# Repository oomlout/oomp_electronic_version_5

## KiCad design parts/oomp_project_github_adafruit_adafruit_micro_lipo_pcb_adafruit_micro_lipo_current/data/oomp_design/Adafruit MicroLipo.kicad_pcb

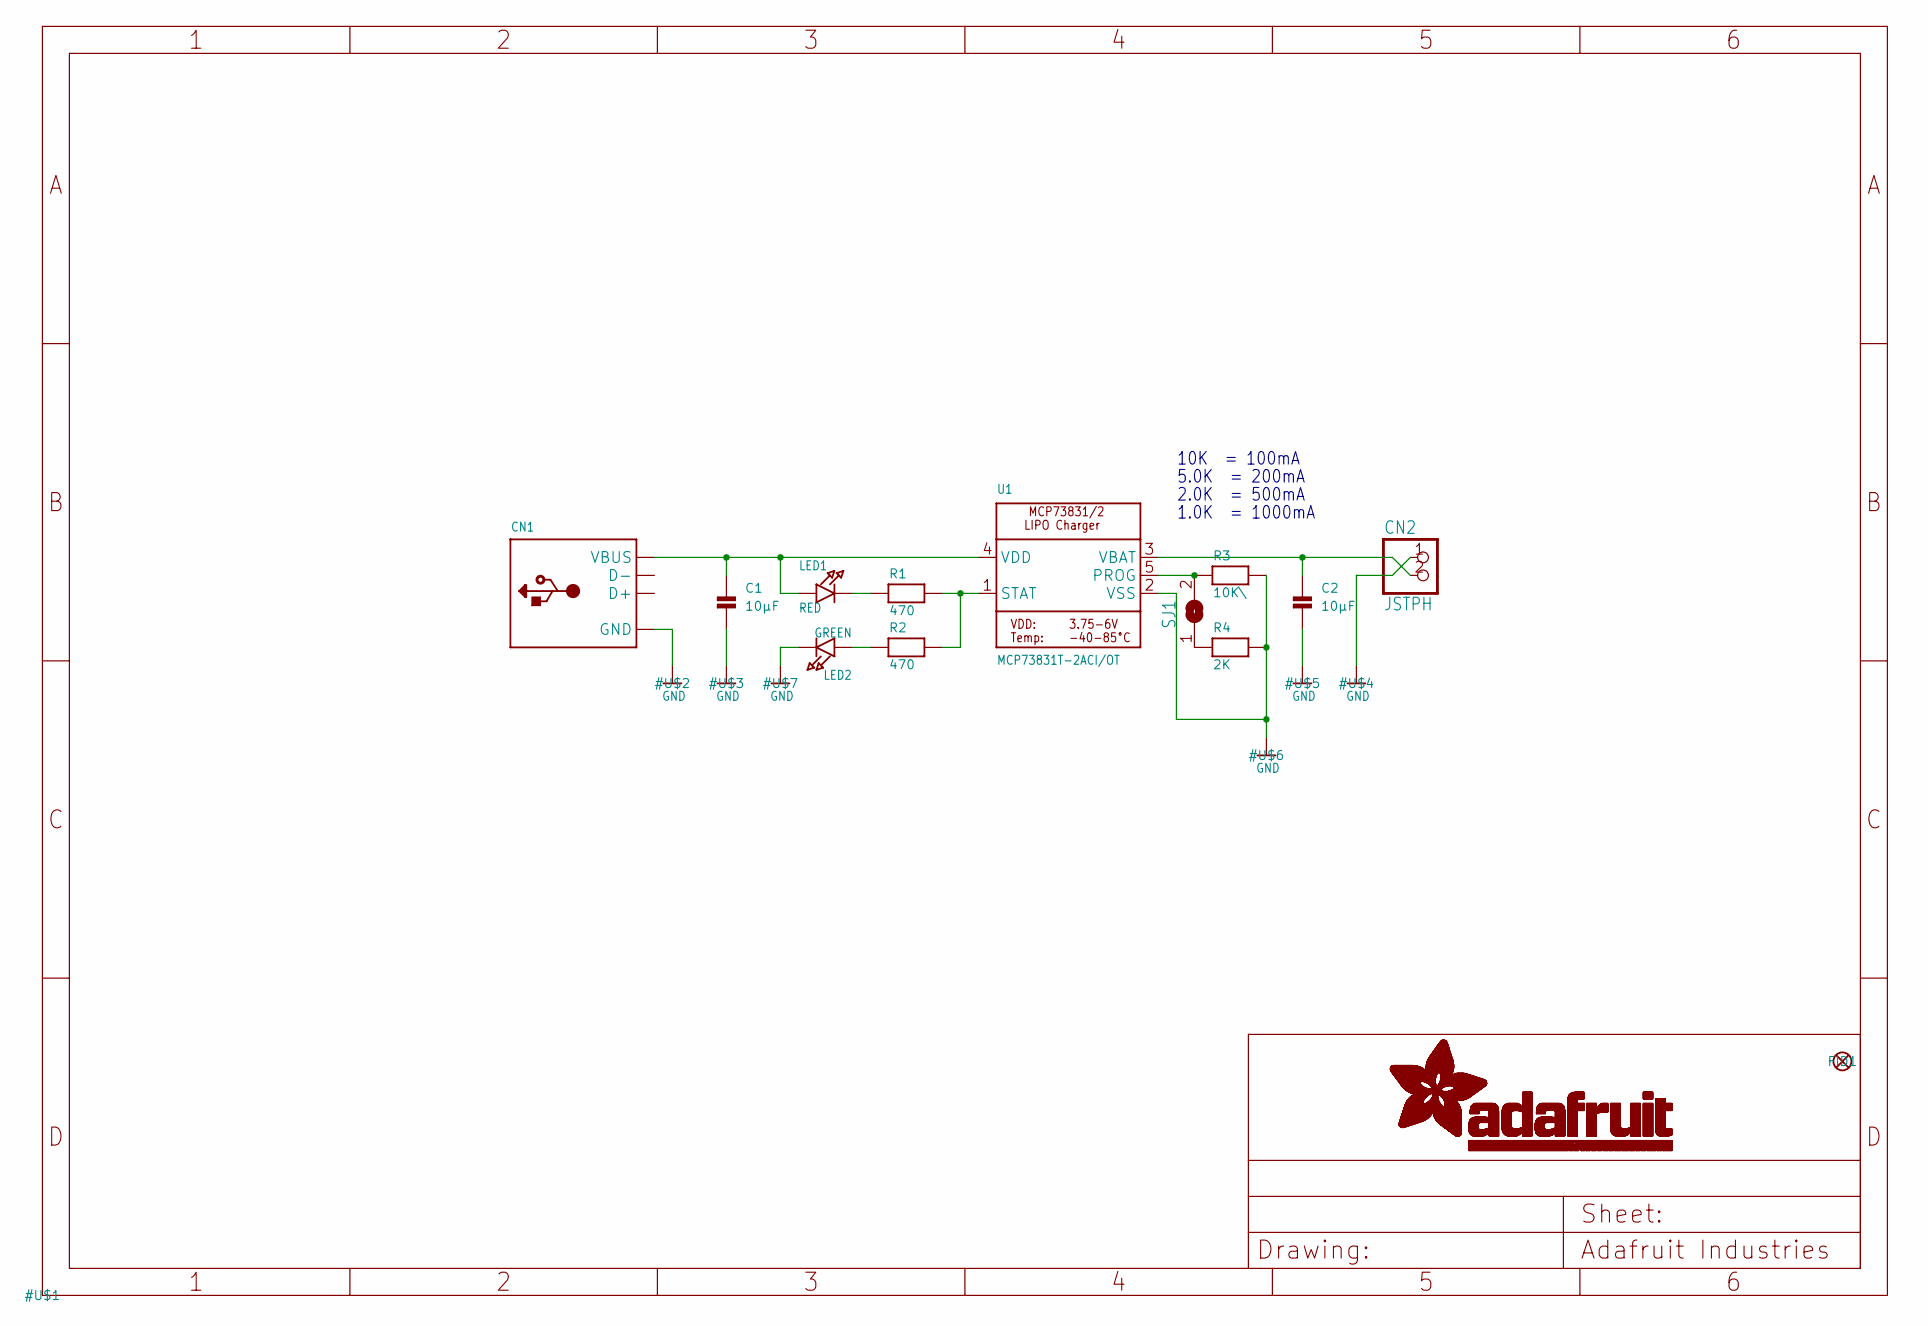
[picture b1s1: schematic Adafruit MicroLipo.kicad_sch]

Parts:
C1, C2: 10µF; 0805
CN1: USB_TYPEAPCB; USBA_PCB
CN2: JSTPH; JSTPH2
FID1: FIDUCIAL""; FIDUCIAL_1MM
LED1: RED; CHIPLED_0805
LED2: GREEN; CHIPLED_0805
R1, R2: 470; 0805
R3: 10K\; 0805
R4: 2K; 0805
SJ1: SOLDERJUMPER; SOLDERJUMPER_ARROW_NOPASTE
U1: MCP73831T-2ACI/OT; SOT23-5

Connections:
GND: C1.2, C2.2, CN1.GND, CN2.1, LED2.C, R3.2, R4.2, U1.2 (VSS)
unnamed: LED1.C, R1.1
unnamed: R1.2, R2.2, U1.1 (STAT)
unnamed: R4.1, SJ1.1
unnamed: R3.1, SJ1.2, U1.5 (PROG)
unnamed: LED2.A, R2.1
VBAT: C2.1, CN2.2, U1.3 (VBAT)
VDD: C1.1, CN1.VCC (VBUS), LED1.A, U1.4 (VDD)

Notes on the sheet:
5.0K = 200mA
10K = 100mA
1.0K = 1000mA
2.0K = 500mA

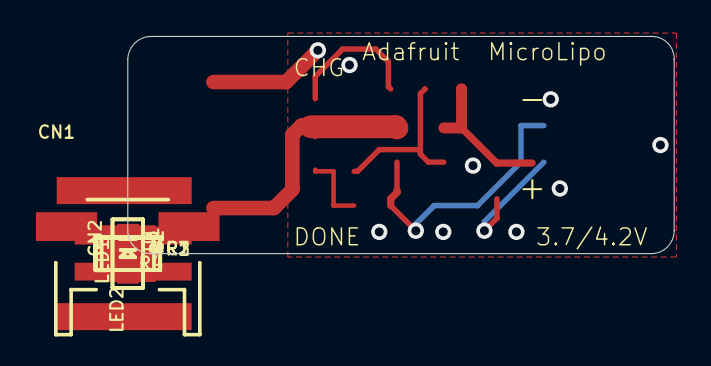
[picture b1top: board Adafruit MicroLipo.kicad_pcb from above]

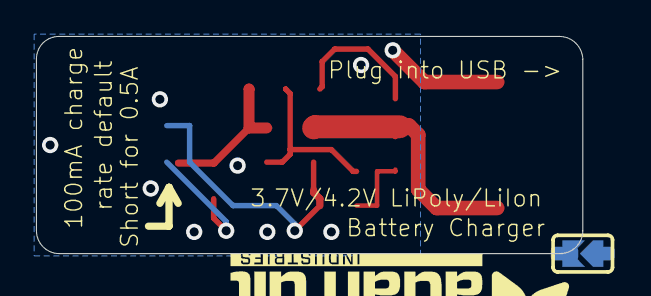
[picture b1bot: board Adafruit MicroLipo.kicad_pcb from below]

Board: 2 copper layers, 30.4 x 12.1 mm, 14 parts (2 on the bottom side), 8 nets.

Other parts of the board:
U$8: ADAFRUIT_TEXT_20MM

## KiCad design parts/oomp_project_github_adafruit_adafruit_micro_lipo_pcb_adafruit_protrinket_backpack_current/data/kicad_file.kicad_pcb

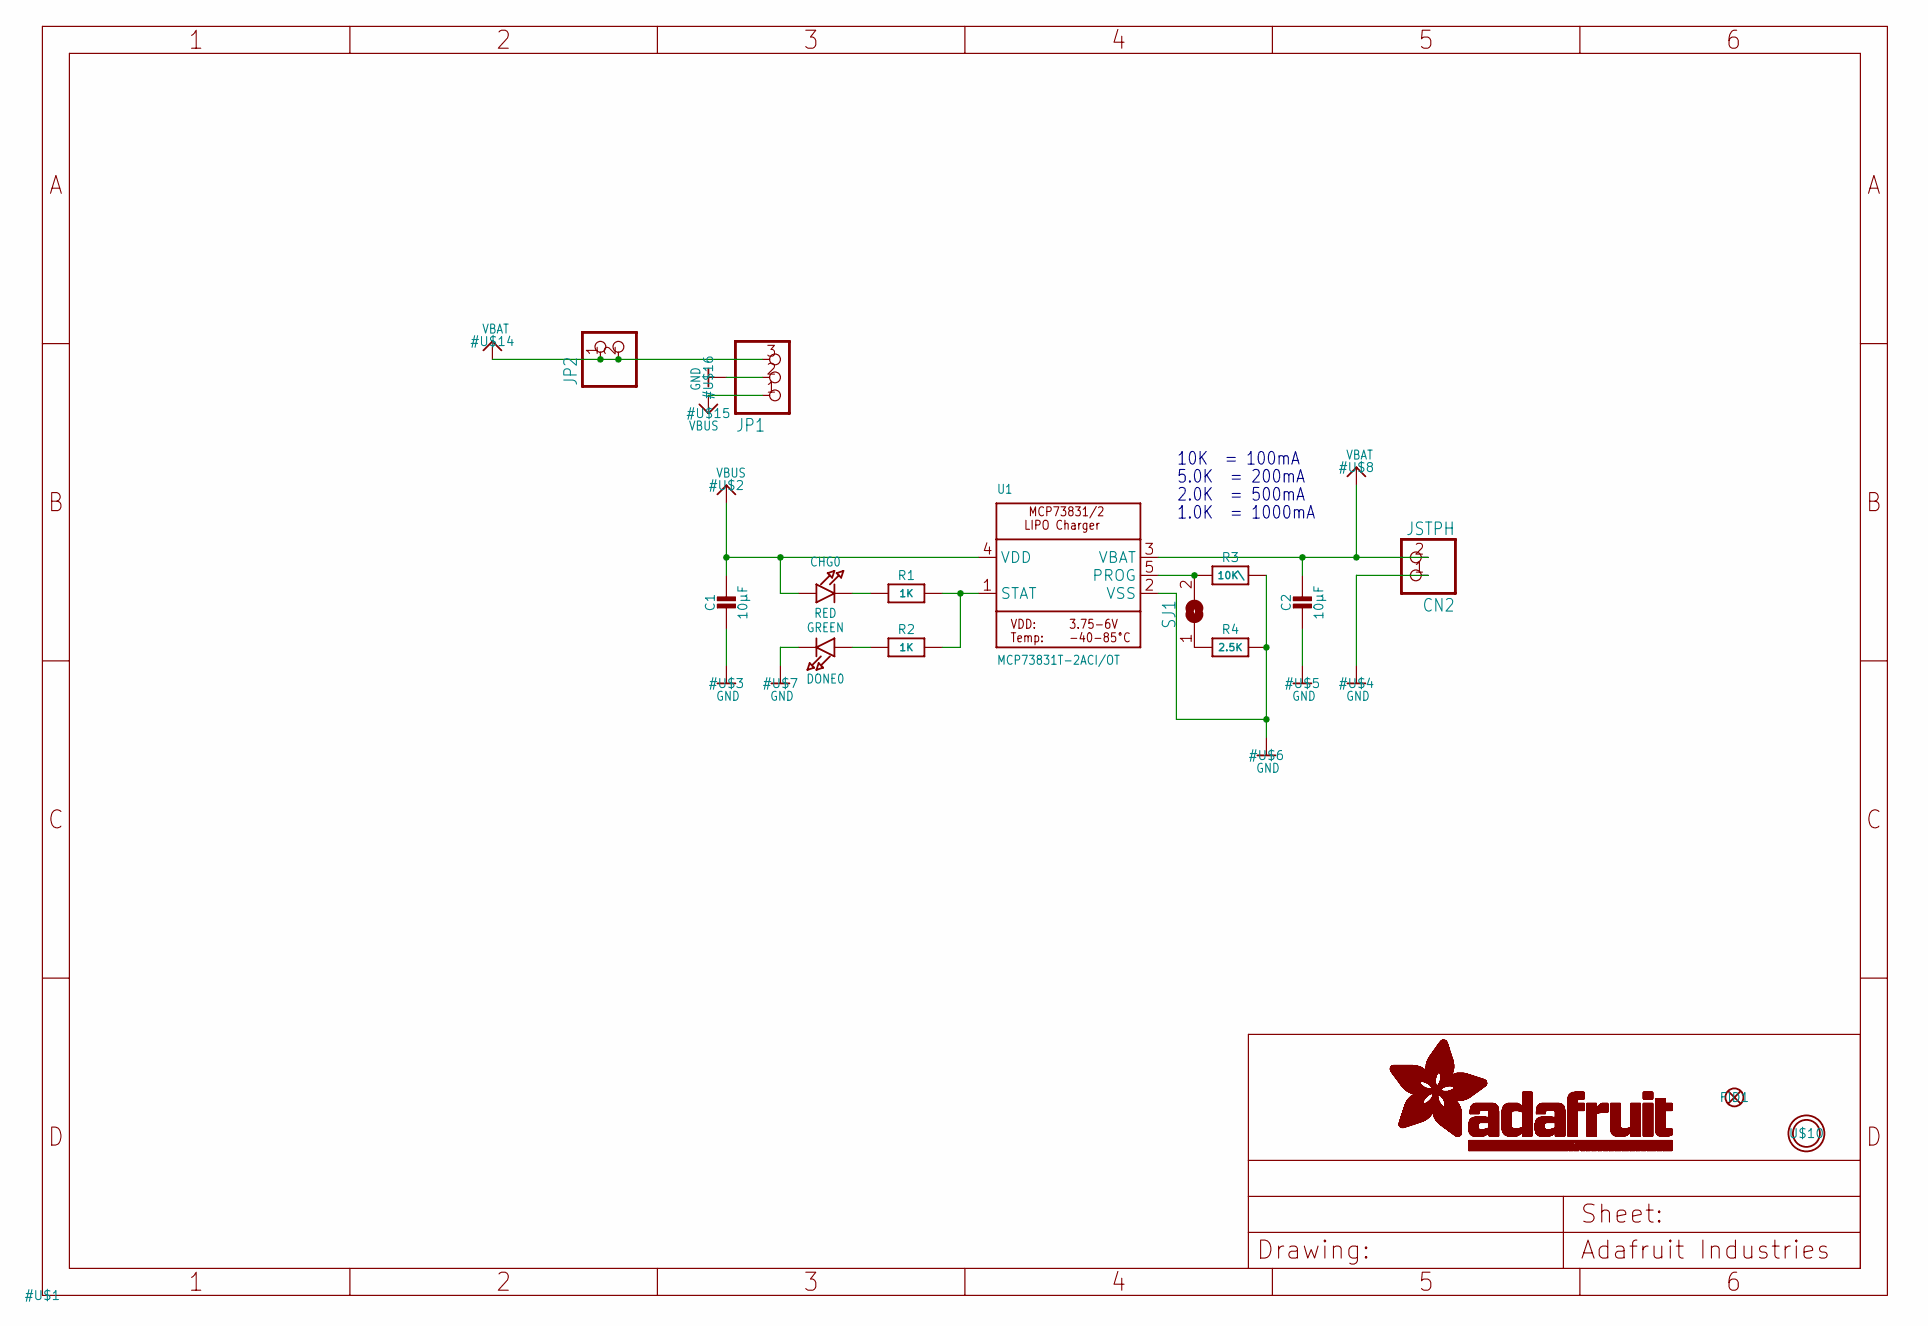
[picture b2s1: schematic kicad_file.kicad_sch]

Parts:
C1, C2: 10µF; 0805-NO
CHG0: RED; CHIPLED_0805_NOOUTLINE
CN2: JSTPH; JSTPH2
DONE0: GREEN; CHIPLED_0805_NOOUTLINE
FID1: FIDUCIAL""; FIDUCIAL_1MM
JP1: HEADER-1X376MIL; 1X03_ROUND_76
JP2: HEADER-1X2ROUND; 1X02_ROUND
R1, R2: 1K; 0805-NO
R3: 10K\; _0805MP
R4: 2.5K; 0805-NO
SJ1: SOLDERJUMPER; SOLDERJUMPER_ARROW_NOPASTE
U1: MCP73831T-2ACI/OT; SOT23-5
U$10: MOUNTINGHOLE2.5; MOUNTINGHOLE_2.5_PLATED

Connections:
GND: C1.2, C2.2, CN2.1, DONE0.C, JP1.2, R3.2, R4.2, U1.2 (VSS)
unnamed: CHG0.C, R1.1
unnamed: R1.2, R2.2, U1.1 (STAT)
unnamed: R4.1, SJ1.1
unnamed: R3.1, SJ1.2, U1.5 (PROG)
unnamed: DONE0.A, R2.1
VBAT: C2.1, CN2.2, JP1.3, JP2.1, JP2.2, U1.3 (VBAT)
VBUS: C1.1, CHG0.A, JP1.1, U1.4 (VDD)

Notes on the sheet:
2.0K = 500mA
1.0K = 1000mA
5.0K = 200mA
10K = 100mA

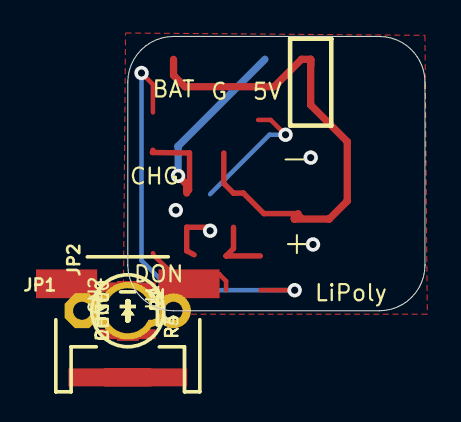
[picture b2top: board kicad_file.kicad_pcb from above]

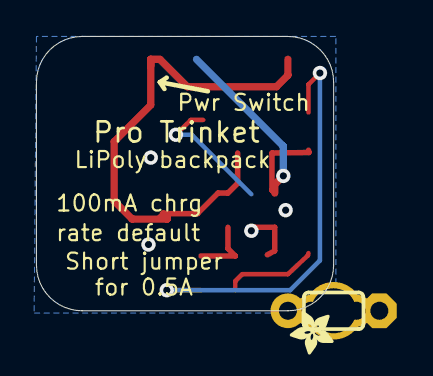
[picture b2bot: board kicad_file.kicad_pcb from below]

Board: 2 copper layers, 16.5 x 15.2 mm, 16 parts (2 on the bottom side), 8 nets.

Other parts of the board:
U$9: ADAFRUIT_2.5MM

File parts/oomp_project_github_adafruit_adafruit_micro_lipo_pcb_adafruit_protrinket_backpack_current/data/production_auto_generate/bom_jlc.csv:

Comment,Designator,Footprint,LCSC Part #
,JP2,Adafruit protrinket backpack-import-fps:1X02_ROUND,C492401
,JP1,Adafruit protrinket backpack-import-fps:1X03_ROUND_76,C49257
,U$9,Adafruit protrinket backpack-import-fps:ADAFRUIT_2.5MM,
10K\,R3,Adafruit protrinket backpack-import-fps:_0805MP,C17414
10µF,"C1,C2",Adafruit protrinket backpack-import-fps:0805-NO,
1K,"R1,R2",Adafruit protrinket backpack-import-fps:0805-NO,C17513
2.5K,R4,Adafruit protrinket backpack-import-fps:0805-NO,
GREEN,DONE0,Adafruit protrinket backpack-import-fps:CHIPLED_0805_NOOUTLINE,
JSTPH,CN2,Adafruit protrinket backpack-import-fps:JSTPH2,
MCP73831T-2ACI/OT,U1,Adafruit protrinket backpack-import-fps:SOT23-5,
RED,CHG0,Adafruit protrinket backpack-import-fps:CHIPLED_0805_NOOUTLINE,
